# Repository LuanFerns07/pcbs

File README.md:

# Open Hardware Projects

Repositório para projetos independentes de hardware aberto. O primeiro é a coleção didática do PET Engenharia Elétrica UFC, em [`projects/pet-eletrica-ufc/`](projects/pet-eletrica-ufc/).

## Organização

- `projects/`: projetos autocontidos, cada um com contexto, documentação e placas.
- `shared/`: automação, bibliotecas e templates realmente reutilizáveis.
- `docs/`: convenções aplicáveis ao repositório inteiro.

Cada placa deve manter seus arquivos-fonte KiCad e documentação junto ao projeto. Relatórios e arquivos de fabricação só devem ser apresentados como resultados quando gerados e revisados com ferramentas reais. Consulte [AGENTS.md](AGENTS.md) antes de contribuir.

## Ambiente observado

No levantamento de 2026-10-27, o worktree estava limpo em `main`, acompanhando `origin/main`. O ambiente é Debian GNU/Linux 13.7, com KiCad, `kicad-cli` e `pcbnew` 9.0.2 instalados. A interface gráfica não foi validada nesta sessão sem `DISPLAY`. Consulte [`projects/pet-eletrica-ufc/PROJECT_CONTEXT.md`](projects/pet-eletrica-ufc/PROJECT_CONTEXT.md) para os limites e decisões do projeto PET.

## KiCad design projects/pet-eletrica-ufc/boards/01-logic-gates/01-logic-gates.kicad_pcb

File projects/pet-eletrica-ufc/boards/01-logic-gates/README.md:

# Placa 01 — Portas lógicas com transistores discretos

Placa didática do PET Engenharia Elétrica UFC com portas **AND, OR e NOT** construídas somente com transistores 2N3904. Cada porta tem entradas por botões independentes, saída elétrica acessível nos pads do circuito e LED indicador. O projeto nativo KiCad é editável; as imagens abaixo mostram a revisão A.

[Vista traseira](renders/01-logic-gates-back.png) · [Prévia 3D ilustrativa](renders/01-logic-gates-3d-preview.png) · [Fotografia de referência](../../assets/reference/logic-gates-reference.png) · [Esquemático PDF](manufacturing/schematic.pdf)

## Estado de engenharia

- KiCad 9.0.2: ERC **0 violações**, DRC **0 violações**, **0 pads sem conexão** e **0 problemas de paridade esquemático/PCB**. Relatórios em `reports/` e `manufacturing/`.
- Comparação independente da netlist com a PCB: **98 identidades de pino/pad e 44 valores/footprints conferidos**, incluindo polaridade do diodo e LEDs e ordem E-B-C do 2N3904.
- ngspice 44.2: **12 pontos DC** (quatro combinações de botões em 4,75, 5,00 e 5,25 V) passaram os limites adotados. O modelo de transistor/LED é simplificado e não substitui medições de protótipo.
- **Nenhuma placa física foi fabricada, montada ou medida.** A revisão A é candidata a protótipo. Conferir componentes reais e prévia do fabricante antes de encomendar.

## Uso e alimentação

Conecte **5 V regulados** em `J1`, pino 1 `+5V` e pino 2 `GND`, com limite de corrente de aproximadamente 100 mA na primeira energização. `D1` (1N5819) está em série para bloquear polaridade invertida; `C1` (100 nF) desacopla a alimentação após o diodo. O circuito não tolera sobretensão sustentada. A entrada de dois pinos foi escolhida pela montagem THT simples e pelo custo; USB-C exigiria receptáculo SMD e resistores `Rd` em CC1 e CC2. Uma fonte USB de 5 V pode ser usada com adaptador polarizado verificado, sem depender de fonte com tensão incomum.

Cada botão fecha a respectiva entrada em `VCC`. Solto, um resistor de 10 kΩ a leva a GND. `SW1/SW2` comandam AND, `SW3/SW4` comandam OR e `SW5` comanda NOT. Os LEDs acendem quando a função vale 1.

| A | B | AND | OR | NOT A |
|---:|---:|---:|---:|---:|
| 0 | 0 | 0 | 0 | 1 |
| 0 | 1 | 0 | 1 | 1 |
| 1 | 0 | 0 | 1 | 0 |
| 1 | 1 | 1 | 1 | 0 |

Os sinais `A_AND`, `B_AND`, `A_OR`, `B_OR` e `A_NOT` são independentes; a tabela combina valores iguais por conveniência didática. Soltar todos os botões equivale à primeira linha.

## Circuito e dimensionamento

`Q1/Q2` em série formam `N_AND`, invertido por `Q3` em `Y_AND`. `Q5/Q6` em paralelo formam `N_OR`, invertido por `Q7` em `Y_OR`. `Q9` é o inversor de emissor comum para `Y_NOT`. `Q4`, `Q8` e `Q10` acionam os LEDs sem colocar sua corrente diretamente nas saídas lógicas. `R13`–`R17` de 2,2 kΩ elevam as saídas; `R3`–`R12` de 10 kΩ limitam corrente de base; `R18`–`R20` de 1,5 kΩ limitam LED. A saída alta carregada pelo resistor de base seguinte é cerca de 4,04 V a 5,00 V de entrada na simulação; a baixa é cerca de 0,05–0,06 V. Os limites didáticos definidos são **baixo ≤0,4 V** e **alto ≥3,5 V**, válidos somente para esta topologia e carga prevista.

A [folha do 2N3904 da onsemi](https://www.onsemi.com/pdf/datasheet/2n3904-d.pdf) especifica a ordem **1 emissor, 2 base, 3 coletor** e `VCE(sat)` máximo de 0,2 V em `IC=10 mA, IB=1 mA`. Aqui o coletor dos inversores recebe no máximo cerca de 2,4 mA e a corrente de base calculada supera aproximadamente 0,28 mA no pior caso analisado. A razão forçada fica abaixo de 10. Esse cálculo é uma margem de projeto, não uma garantia de pior caso para todos os lotes e temperaturas. A [folha do LED TLHR5200](https://www.vishay.com/docs/83011/tlhr5200.pdf) informa `VF` típico de 2 V a 20 mA; a simulação usa um modelo de LED aproximado e indica 1,84–2,17 mA quando aceso. Em curto no LED, o resistor de 1,5 kΩ ainda limita a corrente nominal a menos de 3,7 mA com 5,25 V de entrada e tolerância de −5% do resistor.

A correspondência física `Q_NPN_EBC` ↔ `TO-92_Inline` foi conferida explicitamente. Ver mais hipóteses e cálculos em [PROJECT_CONTEXT.md](../../PROJECT_CONTEXT.md).

## Geometria e serigrafia

Contorno de aproximadamente **123 × 155 mm**, duas camadas, cantos de raio 3 mm. A fotografia não permite extrair medidas precisas; esta revisão preserva sua proporção vertical, os cinco botões à esquerda, os símbolos grandes no centro e LEDs/tabelas à direita. A serigrafia inclui a marca PET derivada do PNG fornecido, título, função dos blocos e revisão. O SVG original de identidade não foi fornecido; o traçado monocromático é uma adaptação para serigrafia, não uma reconstrução de manual de marca.

Solicitar ao fabricante **máscara branca e serigrafia preta**: os Gerbers não codificam cores. O acabamento e contraste precisam ser confirmados na prévia do fabricante. Não há furos de fixação nesta revisão para preservar área útil e fidelidade à referência.

## Montagem e teste com multímetro

1. Separe os componentes conforme [BOM.csv](manufacturing/BOM.csv). Confirme a pinagem **E-B-C** do lote de 2N3904 escolhido e o corpo de 12 × 12 mm dos botões Omron B3F-4050.
2. Solde resistores, diodo, capacitor, transistores, botões, LEDs e conector nessa ordem. Alinhe a faixa de `D1` ao cátodo e o lado chato/cátodo dos LEDs ao pad 1. Não confunda os diodos `D1` e `D2`–`D4`.
3. Com a placa desligada, meça continuidade de GND e ausência de curto entre `+5V` e GND. Inspecione pontes de solda, especialmente nos três pads próximos de cada TO-92.
4. Energize com 5,0 V e limite inicial de aproximadamente 100 mA. Meça `VCC` depois de `D1`, depois as entradas soltas (próximas de 0 V) e pressionadas (próximas de `VCC`).
5. Para cada bloco, pressione as combinações da tabela. Meça `Y_AND`, `Y_OR`, `Y_NOT` e compare com ≤0,4 V / ≥3,5 V; confira se o LED correspondente segue a saída. Um LED apagado não substitui a medida do nó lógico.
6. Desligue imediatamente se houver aquecimento, consumo inesperado ou saída fora da faixa. Anote tensão de alimentação, tensões de saída e corrente antes de concluir o ensaio físico.

## Arquivos e reprodução

- `01-logic-gates.kicad_sch`, `.kicad_pcb`, `.kicad_pro`: fontes nativas.
- `../../scripts/validate_logic_gates.sh`: gera as fontes, executa ERC, DRC, paridade, comparação da netlist e BOM.
- `../../scripts/simulate_logic_gates.py`: DC no ngspice com modelos simplificados; resultados em `reports/simulation.csv`.
- `../../scripts/render_board_previews.py`: usa KiCad CLI, ImageMagick `convert` e Pillow para gerar vistas 2D diretamente da PCB e uma prévia isométrica **ilustrativa**. Os modelos de componentes desenhados nesta imagem são aproximados.
- `../../scripts/export_logic_gates.sh`: repete validação e exporta [manufacturing/](manufacturing/). O modelo STEP/GLB usa o modelo 3D KiCad disponível para cada footprint; os botões usam um modelo de 6 mm escalado para representar o corpo 12 × 12 mm, portanto a geometria 3D deles é apenas aproximada.

O guia de aula e exercícios está em [logic-gates-lab.md](../../docs/logic-gates-lab.md). As pendências da revisão estão em [manufacturing/README.md](manufacturing/README.md).

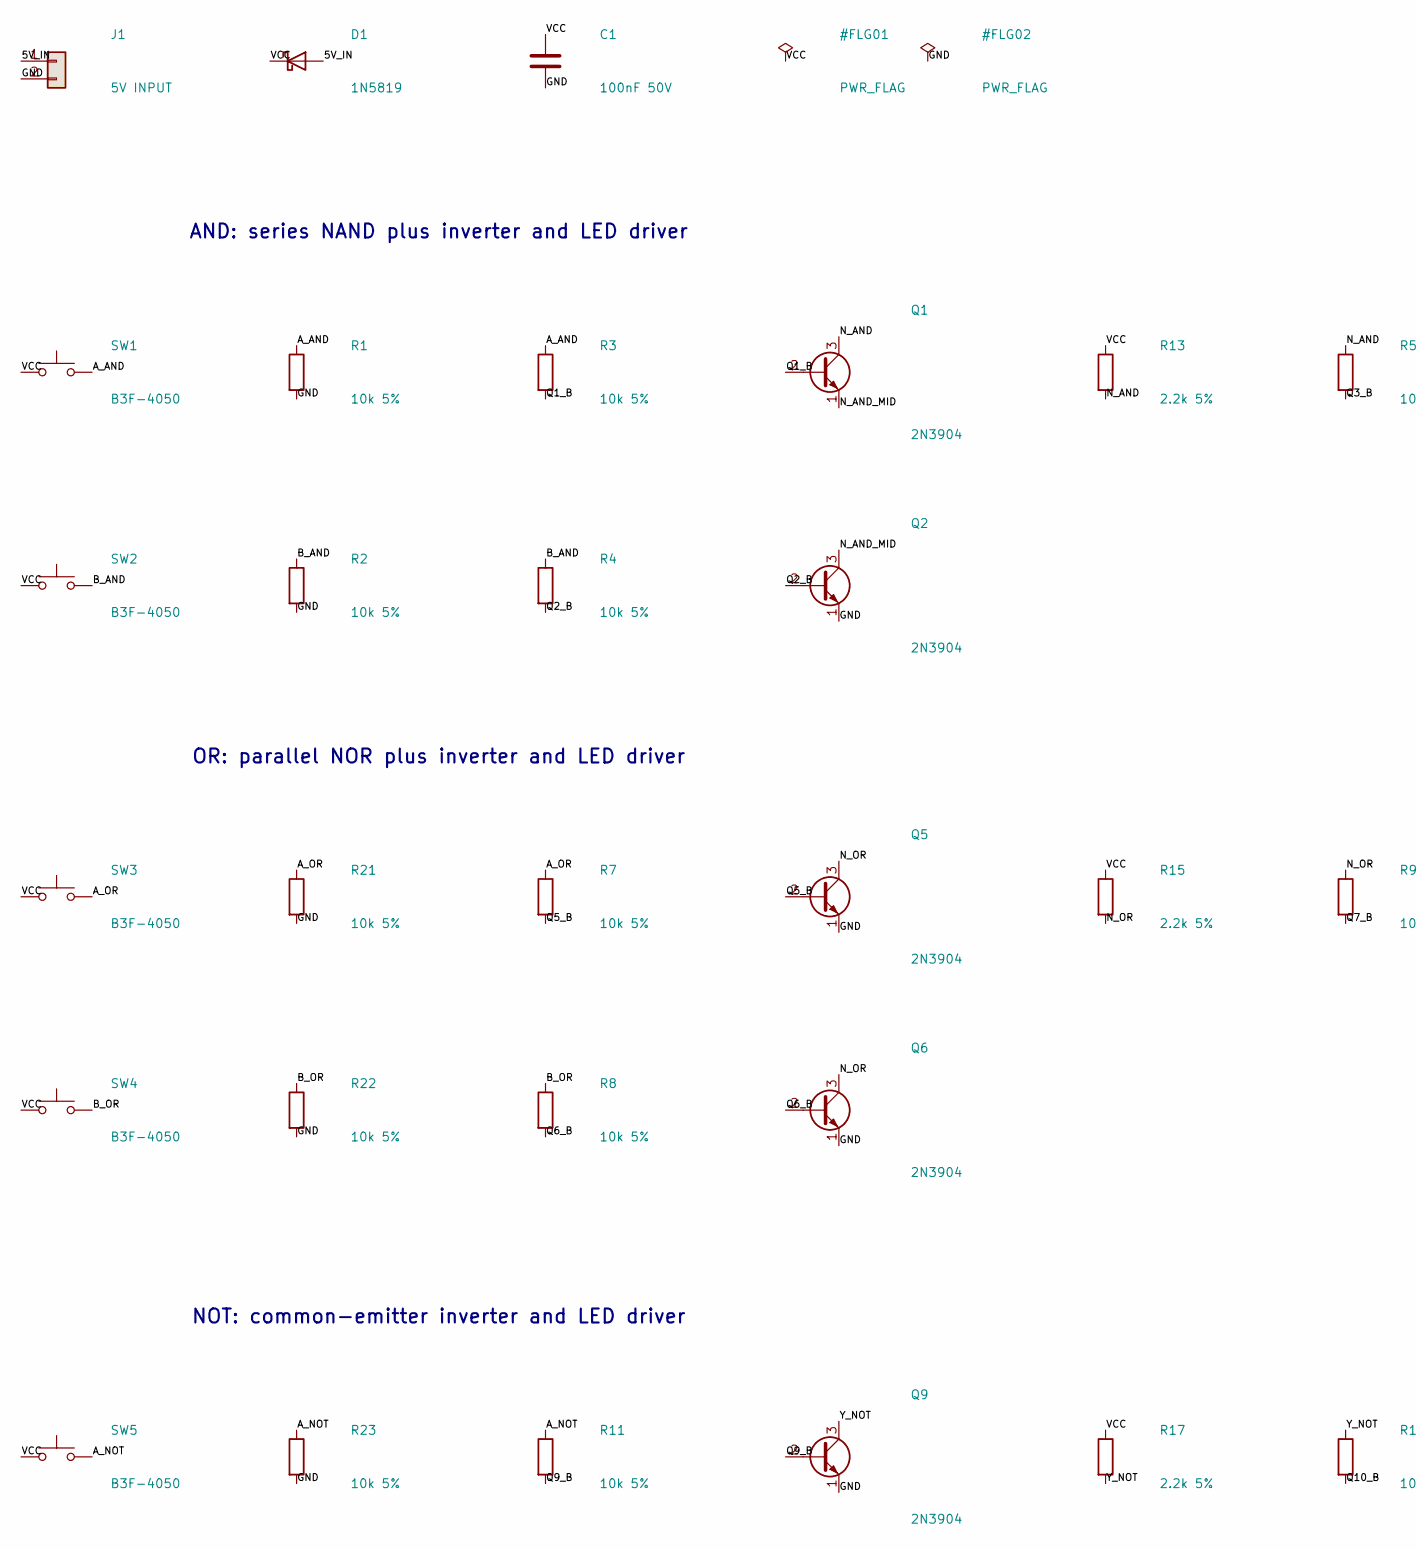
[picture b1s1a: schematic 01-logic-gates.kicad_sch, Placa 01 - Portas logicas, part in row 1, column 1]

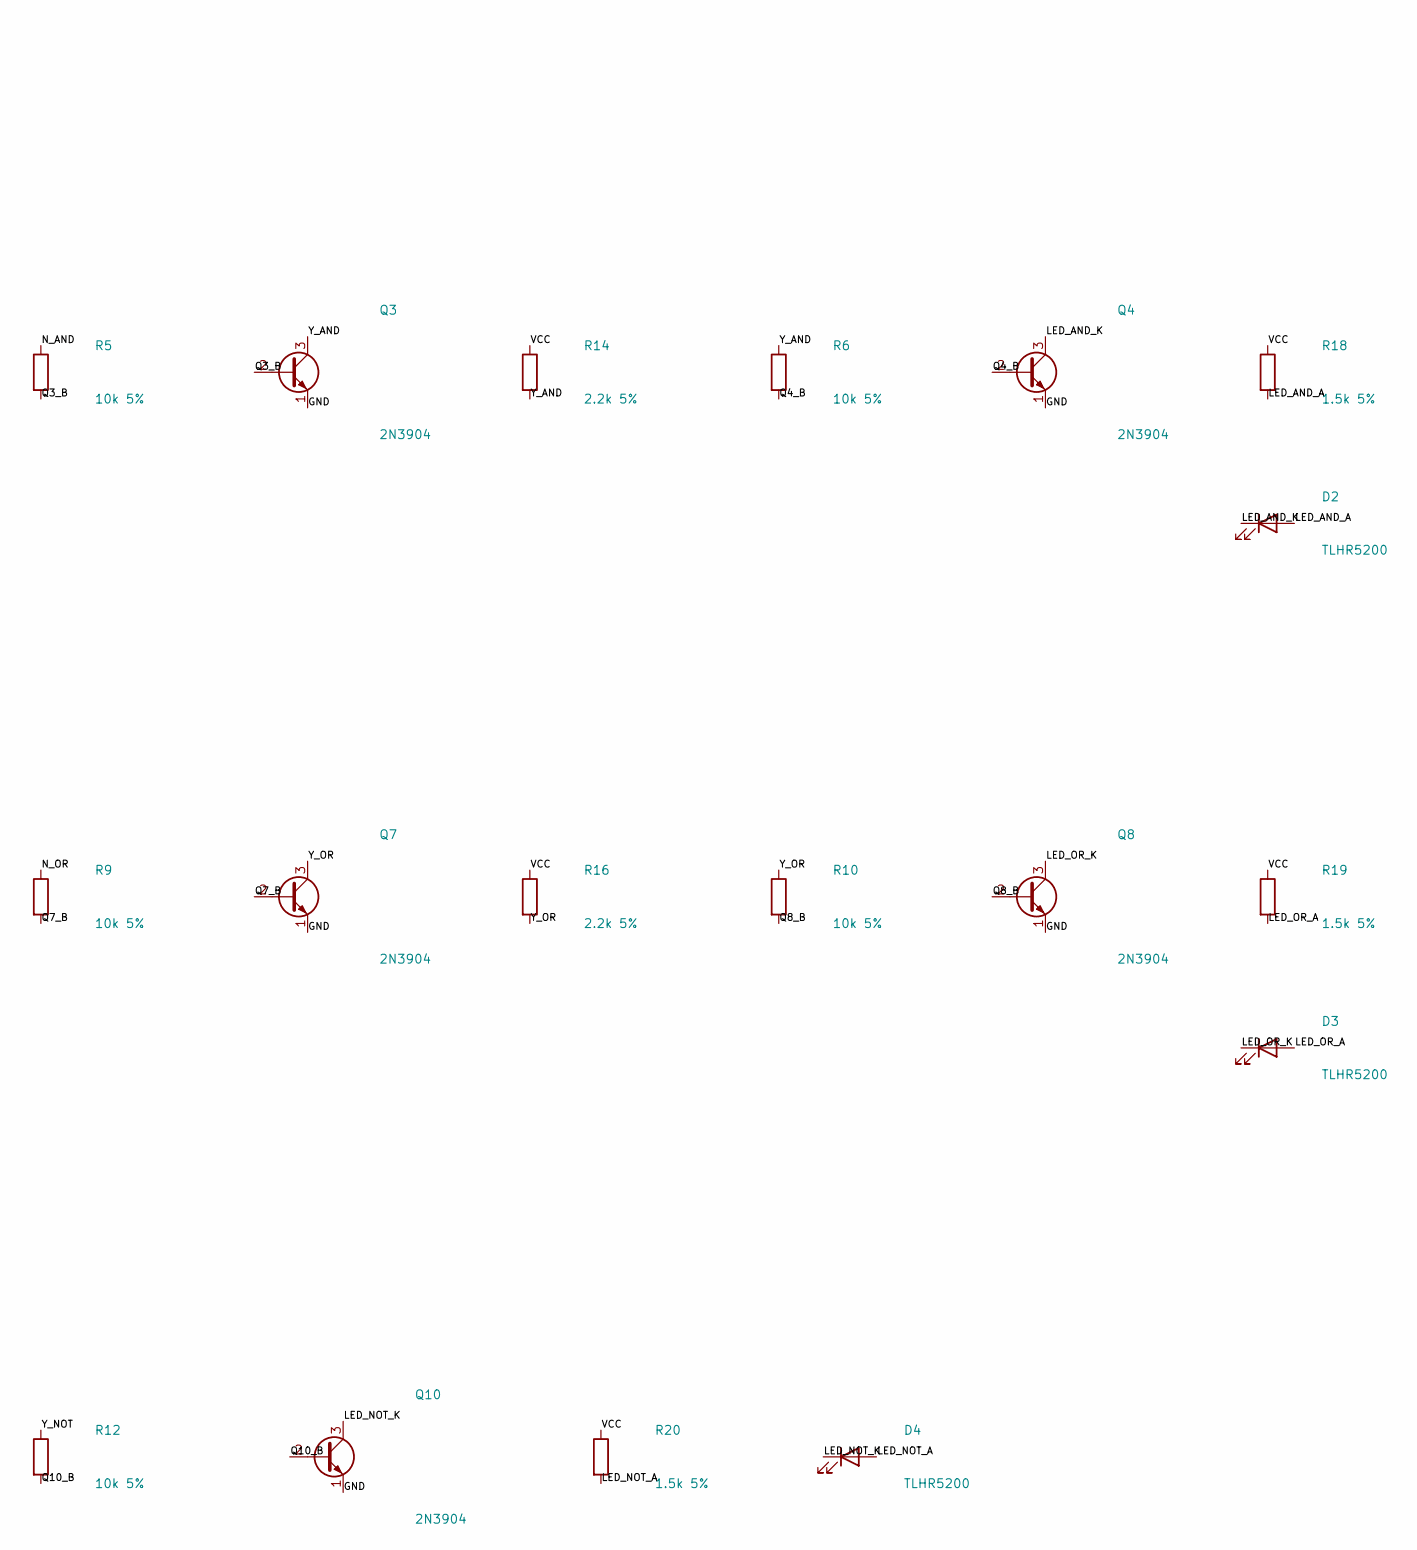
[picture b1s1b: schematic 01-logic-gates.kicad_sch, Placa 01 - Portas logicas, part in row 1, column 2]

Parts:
C1: 100nF 50V; C_Disc_D5.0mm_W2.5mm_P2.50mm
D1: 1N5819; D_DO-41_SOD81_P10.16mm_Horizontal
D2, D3, D4: TLHR5200; LED_D5.0mm
J1: 5V INPUT; PinHeader_1x02_P2.54mm_Vertical
Q1, Q2, Q3, Q4, Q5, Q6, Q7, Q8, Q9, Q10: 2N3904; TO-92_Inline
R1, R2, R3, R4, R5, R6, R7, R8, R9, R10, R11, R12, R21, R22, R23: 10k 5%; R_Axial_DIN0207_L6.3mm_D2.5mm_P10.16mm_Horizontal
R13, R14, R15, R16, R17: 2.2k 5%; R_Axial_DIN0207_L6.3mm_D2.5mm_P10.16mm_Horizontal
R18, R19, R20: 1.5k 5%; R_Axial_DIN0207_L6.3mm_D2.5mm_P10.16mm_Horizontal
SW1, SW2, SW3, SW4, SW5: B3F-4050; SW_SPST_Omron_B3F-50xx

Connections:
/5V_IN: D1.2 (A), J1.1
/A_AND: R1.1, R3.1, SW1.2
/A_NOT: R11.1, R23.1, SW5.2
/A_OR: R7.1, R21.1, SW3.2
/B_AND: R2.1, R4.1, SW2.2
/B_OR: R8.1, R22.1, SW4.2
/GND: C1.2, J1.2, Q2.1 (E), Q3.1 (E), Q4.1 (E), Q5.1 (E), Q6.1 (E), Q7.1 (E), Q8.1 (E), Q9.1 (E), Q10.1 (E), R1.2, R2.2, R21.2, R22.2, R23.2
/LED_AND_A: D2.2 (A), R18.2
/LED_AND_K: D2.1 (K), Q4.3 (C)
/LED_NOT_A: D4.2 (A), R20.2
/LED_NOT_K: D4.1 (K), Q10.3 (C)
/LED_OR_A: D3.2 (A), R19.2
/LED_OR_K: D3.1 (K), Q8.3 (C)
/N_AND: Q1.3 (C), R5.1, R13.2
/N_AND_MID: Q1.1 (E), Q2.3 (C)
/N_OR: Q5.3 (C), Q6.3 (C), R9.1, R15.2
/Q1_B: Q1.2 (B), R3.2
/Q2_B: Q2.2 (B), R4.2
/Q3_B: Q3.2 (B), R5.2
/Q4_B: Q4.2 (B), R6.2
/Q5_B: Q5.2 (B), R7.2
/Q6_B: Q6.2 (B), R8.2
/Q7_B: Q7.2 (B), R9.2
/Q8_B: Q8.2 (B), R10.2
/Q9_B: Q9.2 (B), R11.2
/Q10_B: Q10.2 (B), R12.2
/VCC: C1.1, D1.1 (K), R13.1, R14.1, R15.1, R16.1, R17.1, R18.1, R19.1, R20.1, SW1.1, SW2.1, SW3.1, SW4.1, SW5.1
/Y_AND: Q3.3 (C), R6.1, R14.2
/Y_NOT: Q9.3 (C), R12.1, R17.2
/Y_OR: Q7.3 (C), R10.1, R16.2

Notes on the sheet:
AND: series NAND plus inverter and LED driver
OR: parallel NOR plus inverter and LED driver
NOT: common-emitter inverter and LED driver

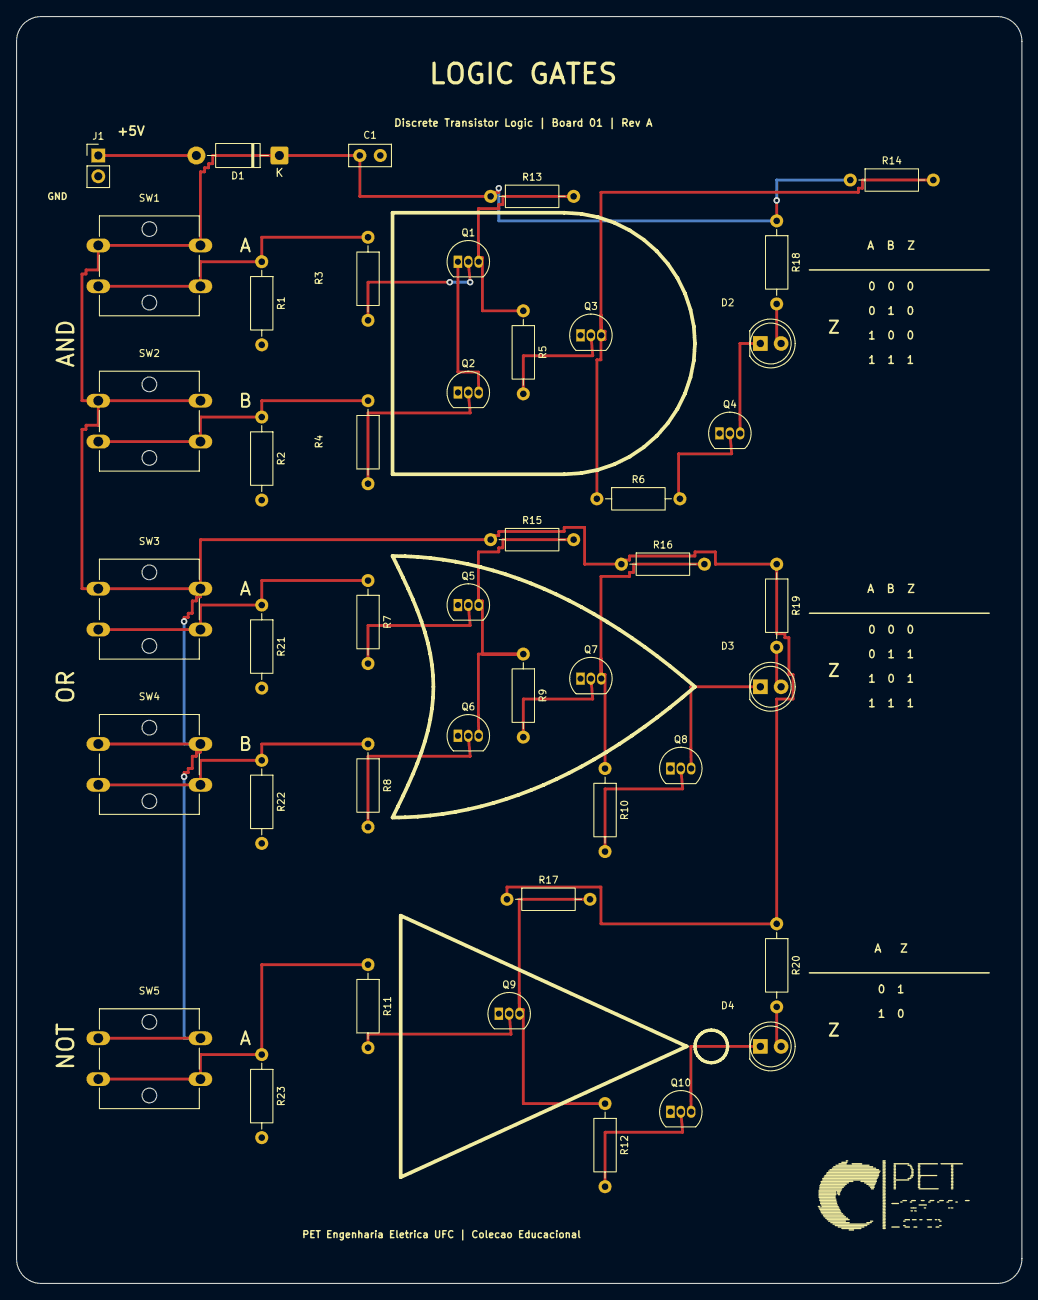
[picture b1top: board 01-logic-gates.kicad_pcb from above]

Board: 2 copper layers, 123.0 x 155.0 mm, 44 parts (0 on the bottom side), 30 nets.

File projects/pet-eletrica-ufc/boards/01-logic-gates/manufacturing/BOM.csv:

"Refs","Value","Footprint","Qty","DNP"
"C1","100nF 50V","Capacitor_THT:C_Disc_D5.0mm_W2.5mm_P2.50mm","1",""
"D1","1N5819","Diode_THT:D_DO-41_SOD81_P10.16mm_Horizontal","1",""
"D2","TLHR5200","LED_THT:LED_D5.0mm","1",""
"D3","TLHR5200","LED_THT:LED_D5.0mm","1",""
"D4","TLHR5200","LED_THT:LED_D5.0mm","1",""
"J1","5V INPUT","Connector_PinHeader_2.54mm:PinHeader_1x02_P2.54mm_Vertical","1",""
"Q1","2N3904","Package_TO_SOT_THT:TO-92_Inline","1",""
"Q2","2N3904","Package_TO_SOT_THT:TO-92_Inline","1",""
"Q3","2N3904","Package_TO_SOT_THT:TO-92_Inline","1",""
"Q4","2N3904","Package_TO_SOT_THT:TO-92_Inline","1",""
"Q5","2N3904","Package_TO_SOT_THT:TO-92_Inline","1",""
"Q6","2N3904","Package_TO_SOT_THT:TO-92_Inline","1",""
"Q7","2N3904","Package_TO_SOT_THT:TO-92_Inline","1",""
"Q8","2N3904","Package_TO_SOT_THT:TO-92_Inline","1",""
"Q9","2N3904","Package_TO_SOT_THT:TO-92_Inline","1",""
"Q10","2N3904","Package_TO_SOT_THT:TO-92_Inline","1",""
"R1","10k 5%","Resistor_THT:R_Axial_DIN0207_L6.3mm_D2.5mm_P10.16mm_Horizontal","1",""
"R2","10k 5%","Resistor_THT:R_Axial_DIN0207_L6.3mm_D2.5mm_P10.16mm_Horizontal","1",""
"R3","10k 5%","Resistor_THT:R_Axial_DIN0207_L6.3mm_D2.5mm_P10.16mm_Horizontal","1",""
"R4","10k 5%","Resistor_THT:R_Axial_DIN0207_L6.3mm_D2.5mm_P10.16mm_Horizontal","1",""
"R5","10k 5%","Resistor_THT:R_Axial_DIN0207_L6.3mm_D2.5mm_P10.16mm_Horizontal","1",""
"R6","10k 5%","Resistor_THT:R_Axial_DIN0207_L6.3mm_D2.5mm_P10.16mm_Horizontal","1",""
"R7","10k 5%","Resistor_THT:R_Axial_DIN0207_L6.3mm_D2.5mm_P10.16mm_Horizontal","1",""
"R8","10k 5%","Resistor_THT:R_Axial_DIN0207_L6.3mm_D2.5mm_P10.16mm_Horizontal","1",""
"R9","10k 5%","Resistor_THT:R_Axial_DIN0207_L6.3mm_D2.5mm_P10.16mm_Horizontal","1",""
"R10","10k 5%","Resistor_THT:R_Axial_DIN0207_L6.3mm_D2.5mm_P10.16mm_Horizontal","1",""
"R11","10k 5%","Resistor_THT:R_Axial_DIN0207_L6.3mm_D2.5mm_P10.16mm_Horizontal","1",""
"R12","10k 5%","Resistor_THT:R_Axial_DIN0207_L6.3mm_D2.5mm_P10.16mm_Horizontal","1",""
"R13","2.2k 5%","Resistor_THT:R_Axial_DIN0207_L6.3mm_D2.5mm_P10.16mm_Horizontal","1",""
"R14","2.2k 5%","Resistor_THT:R_Axial_DIN0207_L6.3mm_D2.5mm_P10.16mm_Horizontal","1",""
"R15","2.2k 5%","Resistor_THT:R_Axial_DIN0207_L6.3mm_D2.5mm_P10.16mm_Horizontal","1",""
"R16","2.2k 5%","Resistor_THT:R_Axial_DIN0207_L6.3mm_D2.5mm_P10.16mm_Horizontal","1",""
"R17","2.2k 5%","Resistor_THT:R_Axial_DIN0207_L6.3mm_D2.5mm_P10.16mm_Horizontal","1",""
"R18","1.5k 5%","Resistor_THT:R_Axial_DIN0207_L6.3mm_D2.5mm_P10.16mm_Horizontal","1",""
"R19","1.5k 5%","Resistor_THT:R_Axial_DIN0207_L6.3mm_D2.5mm_P10.16mm_Horizontal","1",""
"R20","1.5k 5%","Resistor_THT:R_Axial_DIN0207_L6.3mm_D2.5mm_P10.16mm_Horizontal","1",""
"R21","10k 5%","Resistor_THT:R_Axial_DIN0207_L6.3mm_D2.5mm_P10.16mm_Horizontal","1",""
"R22","10k 5%","Resistor_THT:R_Axial_DIN0207_L6.3mm_D2.5mm_P10.16mm_Horizontal","1",""
"R23","10k 5%","Resistor_THT:R_Axial_DIN0207_L6.3mm_D2.5mm_P10.16mm_Horizontal","1",""
"SW1","B3F-4050","Button_Switch_THT:SW_SPST_Omron_B3F-50xx","1",""
"SW2","B3F-4050","Button_Switch_THT:SW_SPST_Omron_B3F-50xx","1",""
"SW3","B3F-4050","Button_Switch_THT:SW_SPST_Omron_B3F-50xx","1",""
"SW4","B3F-4050","Button_Switch_THT:SW_SPST_Omron_B3F-50xx","1",""
"SW5","B3F-4050","Button_Switch_THT:SW_SPST_Omron_B3F-50xx","1",""
